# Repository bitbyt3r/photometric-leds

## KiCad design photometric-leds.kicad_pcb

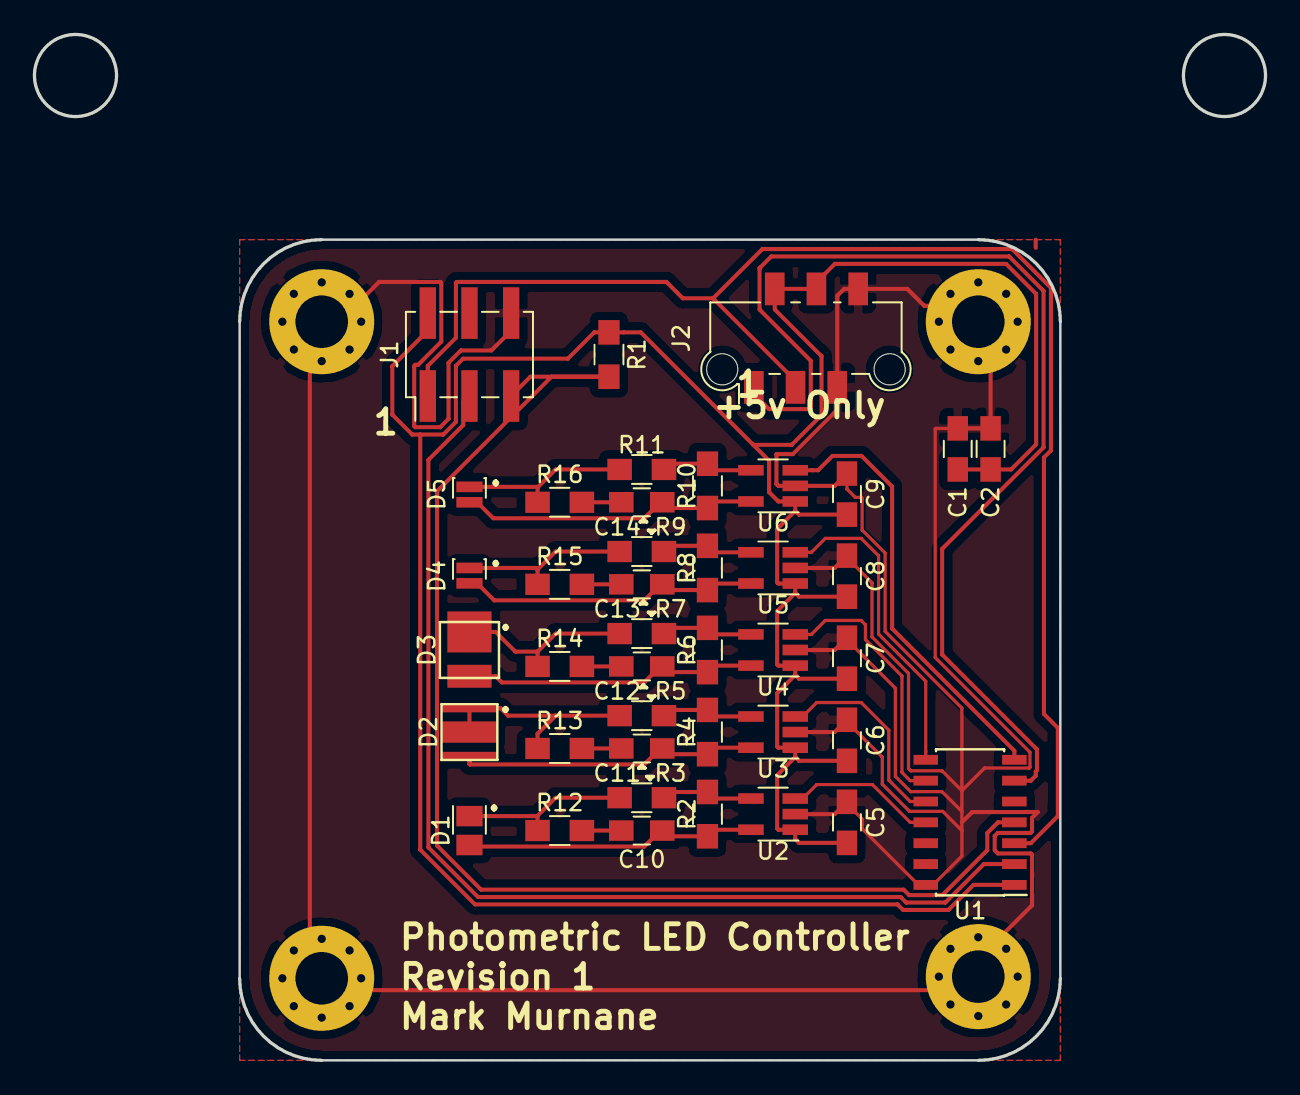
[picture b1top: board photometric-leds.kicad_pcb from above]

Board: 2 copper layers, 75.0 x 62.5 mm, 45 parts (0 on the bottom side), 31 nets.

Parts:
C1: 10uF; C_0805_HandSoldering
C2: 0.1uF; C_0805_HandSoldering
C5, C6, C7, C8, C9: 1uF; C_0805_HandSoldering
C10, C11, C12, C13, C14: 2.2uF; C_0805_HandSoldering
D1: LED; LED_Cree-XQ_HandSoldering
D2: LED; XLamp_XPE2
D3: LED; LUXEON_3535L
D4, D5: LED; LED_0606
J1: CONN_02X03; Pin_Header_Straight_2x03_Pitch2.54mm_SMD
J2: CONN_02X03; Molex_Picoflex_90814_06x1.27mm_Straight
MK1, MK2, MK3, MK4: Mounting_Hole_PAD; MountingHole_3.2mm_M3_Pad_Via
R1: 10k; R_0805_HandSoldering
R2, R4, R6, R8, R10: R; R_0805_HandSoldering
R3, R5, R7, R9, R11: 33k; R_0805_HandSoldering
R12, R13, R14, R15, R16: 0.5; R_0805_HandSoldering
U1: ATTINY20-SSU; SOIC-14_3.9x8.7mm_Pitch1.27mm
U2, U3, U4, U5, U6: pam2800; SOT-23-5_HandSoldering

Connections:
+5V: C1.1, C2.1, C5.1, C6.1, C7.1, C8.1, C9.1, J1.2, J2.2, J2.4, R1.1, U1.1, U2.1, U3.1, U4.1, U5.1, U6.1
GND: C1.2, C2.2, C5.2, C6.2, C7.2, C8.2, C9.2, J1.6, J2.5, J2.6, MK1.1, MK2.1, MK3.1, MK4.1, U1.14, U2.2, U3.2, U4.2, U5.2, U6.2
unnamed: C10.1, D1.2, R2.1, U2.5
unnamed: C10.2, R12.2
unnamed: C11.1, D2.2, R4.1, U3.5
unnamed: C11.2, R13.2
unnamed: C12.1, D3.2, R6.1, U4.5
unnamed: C12.2, R14.2
unnamed: C13.1, D4.2, R8.1, U5.5
unnamed: C13.2, R15.2
unnamed: C14.1, D5.2, R10.1, U6.5
unnamed: C14.2, R16.2
unnamed: D1.1, R3.2, R12.1
unnamed: D2.1, R5.2, R13.1
unnamed: D3.1, R7.2, R14.1
unnamed: D4.1, R9.2, R15.1
unnamed: D5.1, R11.2, R16.1
unnamed: J1.1, J2.3, U1.3
unnamed: J1.3, U1.2
unnamed: J1.5, R1.2, U1.4
unnamed: J2.1, U1.6
unnamed: R2.2, R3.1, U2.4
unnamed: R4.2, R5.1, U3.4
unnamed: R6.2, R7.1, U4.4
unnamed: R8.2, R9.1, U5.4
unnamed: R10.2, R11.1, U6.4
unnamed: U1.7, U6.3
unnamed: U1.8, U5.3
unnamed: U1.9, U4.3
unnamed: U1.10, U3.3
unnamed: U1.11, U2.3

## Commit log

2019-07-15 Added mechanical drawings
